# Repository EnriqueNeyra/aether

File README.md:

# Aether

### Aether is a comprehensive air quality monitor by [**Syntropy Labs**](https://syntropylabs.io/products/aether-air-quality-monitor) built around an ESP32-C3, a Sensirion SEN66 sensor, and a 3.7" e-paper display. It measures **CO2, Temperature, Humidity, PM1.0, PM2.5, PM4.0, PM10, VOC index, and NOx index**, and exposes those readings on-device, on the local network, and through Home Assistant.

## Repo Guide

| Path                      | Contents                                                                   |
| ------------------------- | -------------------------------------------------------------------------- |
| `firmware/`               | ESPHome configuration, custom components, web UI sources, and display code |
| `hardware/pcb/`           | KiCad PCB project                                                          |
| `hardware/manufacturing/` | PCB manufacturing outputs, BOM, and centroid files                         |
| `hardware/datasheets/`    | Reference datasheets used during hardware design                           |
| `enclosure/`              | SolidWorks enclosure and assembly files                                    |
| `manifests/`                  | Firmware manifests for OTA and WebUSB                      |
| `www/`                        | The combined WebUSB flasher and Quick Start Guide site     |

## Contents

- [Features](#features)
- [Hardware](#hardware)
- [Assembly](#assembly)
- [Firmware Setup](#firmware-setup)
  - [Flashing firmware onto a device](#flashing-firmware-onto-a-device)
  - [Firmware development](#firmware-development)
- [Using Aether](#using-aether)
  - [Normal operation](#normal-operation)
  - [Wi-Fi setup and behavior](#wi-fi-setup-and-behavior)
  - [Side button behavior](#side-button-behavior)
  - [Local web UI](#local-web-ui)
  - [Apple HomeKit](#apple-homekit)
  - [Home Assistant & ESPHome API](#home-assistant--esphome-api)
  - [Updates](#updates)
- [License](#license)

## Features

- Measures CO2, Temperature, Humidity, PM1.0, PM2.5, PM4.0, PM10, VOC index, and NOx index using the **Sensirion SEN66**
- Displays live readings on a **416x240 3.7" e-paper panel**
- Serves a **local web dashboard** from the device itself
- Pairs natively with **Apple HomeKit** — no hub, bridge, or Home Assistant required
- Supports **ESPHome / Home Assistant** integration
- Supports **USB factory flashing**, **firmware recovery**, and **OTA updates**
- Fully local, and can run **with or without Wi-Fi**

## Hardware

To build one Aether unit, the following core parts are needed:

| Part                                       | Link                                                                                                                                                                                                                                          |
| ------------------------------------------ | --------------------------------------------------------------------------------------------------------------------------------------------------------------------------------------------------------------------------------------------- |
| **Aether PCB**                             | [Syntropy Labs Store](https://syntropylabs.io/products/aether-air-quality-monitor-custom-pcb) (PCB files available in [`hardware/`](https://github.com/EnriqueNeyra/aether/tree/main/hardware/manufacturing) folder)                          |
| **3.7" e-paper display module**            | [Good Display](https://buy-lcd.com/products/37-inch-416x240-e-paper-black-and-white-spi-fast-refresh-electronic-eink-display-screen-esl-gdey037t03?VariantsId=10346) / [Elecrow](https://www.elecrow.com/3-7-inch-240-416-e-paper-display-black-white-e-ink-display-with-spi-communication.html?srsltid=AfmBOorEN78tDAbaNR6usiU2un_OspDES5jOZ0fWlxrPbxKdn6s-n3yS) |
| **Sensirion SEN66** air quality sensor     | [Sensirion](https://sensirion.com/products/catalog/SEN66) |
| **Reverse 6-pin JST-GH cable**             | [Adafruit](https://www.adafruit.com/product/5754?srsltid=AfmBOopcC6siE6KqjNqU-nj7AwIrnvlDSqnL19iwFrZ47O6lRIhqRYC8) / [AliExpress](https://www.aliexpress.us/w/wholesale-jst-gh-1.25mm-connector-6-pin-reverse.html?spm=a2g0o.detail.search.0) |
| **3D-printed enclosure parts**             | [`enclosure/`](https://github.com/EnriqueNeyra/aether/tree/main/enclosure) |
| **2x M3 x 6 mm countersunk screws + nuts** | [Screws](https://amzn.to/3SKvOgg) / [Nuts](https://amzn.to/44jUIG1) |

<sub>As an Amazon Associate I earn from qualifying purchases.</sub>

### Alternative Display Compatibility

The Aether PCB implements the standard 24-pin FPC e-paper interface. While designed for the 3.7" GDEY037T03, it is hardware-compatible with many other common e-paper panels (e.g., those using SSD1680, UC8151D, and IL0373 driver ICs). **Please note that these alternative displays have not yet been tested or confirmed to work with this device.**

If you choose to use an alternative display, you will need to:
1. **Update the firmware** to instantiate the correct `GxEPD2` display driver class.
2. **Modify the enclosure design** to physically fit the new panel dimensions.

For specific supported ICs and detailed firmware instructions, see [display-compatibility.md](display-compatibility.md).

## Assembly

High-level assembly flow:

### 1. Press-fit the SEN66 into the enclosure body.

### 2. Connect the e-paper display to the PCB with the FPC connector.

### 3. Press-fit the PCB into the enclosure body.

### 4. Connect 6-pin JST GH Cable.

### 5. Bring display over in position above the PCB.

### 6. Attach the display cover.

### 7. Secure the assembly from the bottom with the two M3 fasteners.

## Firmware Setup
_Any Aether devices purchased through [**Syntropy Labs**](https://syntropylabs.io/) are pre-flashed with device firmware and fully tested_

### Flashing firmware onto a device

#### For a new board or a device that needs recovery:

1. Connect Aether to your computer over USB.
2. Open the [Aether WebUSB flashing tool](https://aether.syntropylabs.io/) and go to **Firmware & Updates**.
3. Click **Install Aether firmware** under **Install or Update over USB**.
4. Keep the page open until flashing is complete.
5. Let the device boot.

#### For a device that is already set up and just needs newer firmware:

- **Over Wi-Fi (recommended):** open the device's [local web UI](#local-web-ui), go to **Firmware & updates**, and click **Update**. Home Assistant offers the same update.
- **Over USB:** follow the steps above. When the connected device is already running Aether firmware, the flasher offers an **update** that keeps your Wi-Fi and settings instead of erasing the device.

_Note: The flashing page in `www/` is built around **ESP Web Tools / Web Serial** and requires desktop **Chrome or Edge**._

### Firmware development

If you are working on the ESPHome firmware, use the **latest ESPHome release**. Releases are built with it, and CI checks every PR against it. The default PlatformIO toolchain needs Python 3.12–3.14:

```sh
pip install --upgrade esphome
git clone https://github.com/EnriqueNeyra/aether.git
cd aether/firmware
```

```sh
esphome config aether.yaml
esphome compile aether.yaml
esphome run aether.yaml
```

Release firmware can't be flashed over Wi-Fi. To iterate over Wi-Fi, flash `aether-dev.yaml` over USB once, then use `esphome run aether-dev.yaml --device <device-ip>`.

To try ESPHome's native ESP-IDF toolchain (the default once `toolchain: platformio` is removed in ESPHome 2027.2.0), pass `-s toolchain esp-idf`, e.g. `esphome -s toolchain esp-idf compile aether.yaml`.

## Using Aether

### Normal operation

Once powered, Aether reads the SEN66 and refreshes both the on-device display and the local web dashboard. Temperature can be shown in either **Fahrenheit** or **Celsius**.

### Wi-Fi setup and behavior

On boot, Aether will expose a temporary setup access point so you can connect it to Wi-Fi through the captive portal flow. The network will appear as **aether-XXXXXX**. 

- If you want **local web UI access**, **network-based ota updates**, or **Home Assistant integration**, connect the device to Wi-Fi during setup.
- If you do **not** configure Wi-Fi, the device will still work as a standalone monitor **fully offline**.

Once connected to the access point, you will automatically be redirected to the captive portal. Select your network and enter the password to connect. Once connected to Wi-Fi, the device also hosts its [local web UI](#local-web-ui) at **aether-XXXXXX.local** or the **device's local IP**.

### Side button behavior

The side / boot button supports multiple actions:

- **Short press (tap, under 1 second):** cycles normal dashboard → info screen → HomeKit setup screen → normal dashboard
- **Long press (hold ~3 seconds) from the normal screen:** enters factory reset confirmation
- **Long press (hold ~3 seconds) again on the reset screen:** confirms the factory reset flow
- **Long press (hold ~3 seconds) on the info screen while Wi-Fi is not connected:** reboots the device, which brings the setup access point back after offline mode

Long presses on the info and HomeKit screens never start a factory reset.

### Local web UI

When Aether is on your network, it serves a local browser-based dashboard directly from the device. That UI includes:

- A live environment view for sensor readings
- Temperature unit switching
- Firmware version and update status
- A way to trigger firmware updates from the device UI

### Apple HomeKit

Aether pairs directly with the Home app over Wi-Fi, with no bridge, hub or Home Assistant needed. Home Assistant keeps working alongside it.

To pair, connect Aether to the same Wi-Fi network as your iPhone, iPad or Mac, press the side button twice to show the **HomeKit Setup** screen, then in the Home app tap **+** → **Add Accessory** and scan the QR code. Each Aether has its own setup code, shown only on that screen.

Aether appears as a bridge with four accessories: Temperature, Humidity, CO2 (with an alert above 1000 ppm), and Air Quality (PM2.5, PM10, VOC and NOx, plus an overall rating from the worst of PM2.5, VOC and CO2). They also work in Home widgets, Siri and automations.

- **PM1.0 and PM4.0** aren't exposed, because HomeKit has no characteristic for them.
- **VOC and NOx** are Sensirion's unitless 1–500 indexes, but the Home app labels them in µg/m³.
- HomeKit firmware has no **Bluetooth Wi-Fi setup**, since both don't fit in flash. Use the setup network or USB instead.

### Home Assistant & ESPHome API

Because Aether runs ESPHome, it features a native API over Wi-Fi. This allows for:

- **Automatic Home Assistant Integration:** Aether will automatically appear in Home Assistant integrations dashboard once connected to your network. It exposes all 9 sensor metrics (CO2, temperature, humidity, PM1.0, PM2.5, PM4.0, PM10, VOC index, and NOx index).

<p align="center">
  
</p>

- **Custom Integrations:** You can integrate Aether into your own software or scripts using its local HTTP API. Exposed endpoints include:
  - `GET /api/state` - Returns a JSON object with all current sensor metrics and device status.
  - `POST /api/temp_unit?unit=C|F` - Changes the preferred temperature unit.
  - `POST /api/check_update` - Asks the device to re-check for a firmware update now.
  - `POST /api/perform_update` - Triggers the device to immediately begin downloading and installing the latest firmware update over HTTPS (if one is available).

### Updates

Aether supports more than one update path:

- **Local USB flashing** through the [WebUSB flashing tool](https://aether.syntropylabs.io/) (source located in `www/`)
- **In-device update flow** through the local web UI
- **Home Assistant** when the device is online

Use the USB flashing page for first-time setup and recovery. Use the local web UI for routine updates on devices that are already deployed.

## License

Aether is licensed per directory:

- **Firmware** (`firmware/`): [GNU General Public License v3](firmware/LICENSE). The firmware is built on GPLv3 code (ESPHome's C++ runtime and the GxEPD2 display driver), so it and the firmware binaries built from it are distributed under GPLv3.
- **Everything else** (hardware, PCB and manufacturing files, enclosure, website, and documentation): [Creative Commons Attribution-NonCommercial-ShareAlike 4.0 International License](http://creativecommons.org/licenses/by-nc-sa/4.0/). See [LICENSE](LICENSE).

Third-party components keep their own licenses, including the fonts in `firmware/components/aether_epaper/fonts/` and the libraries the firmware is built with.

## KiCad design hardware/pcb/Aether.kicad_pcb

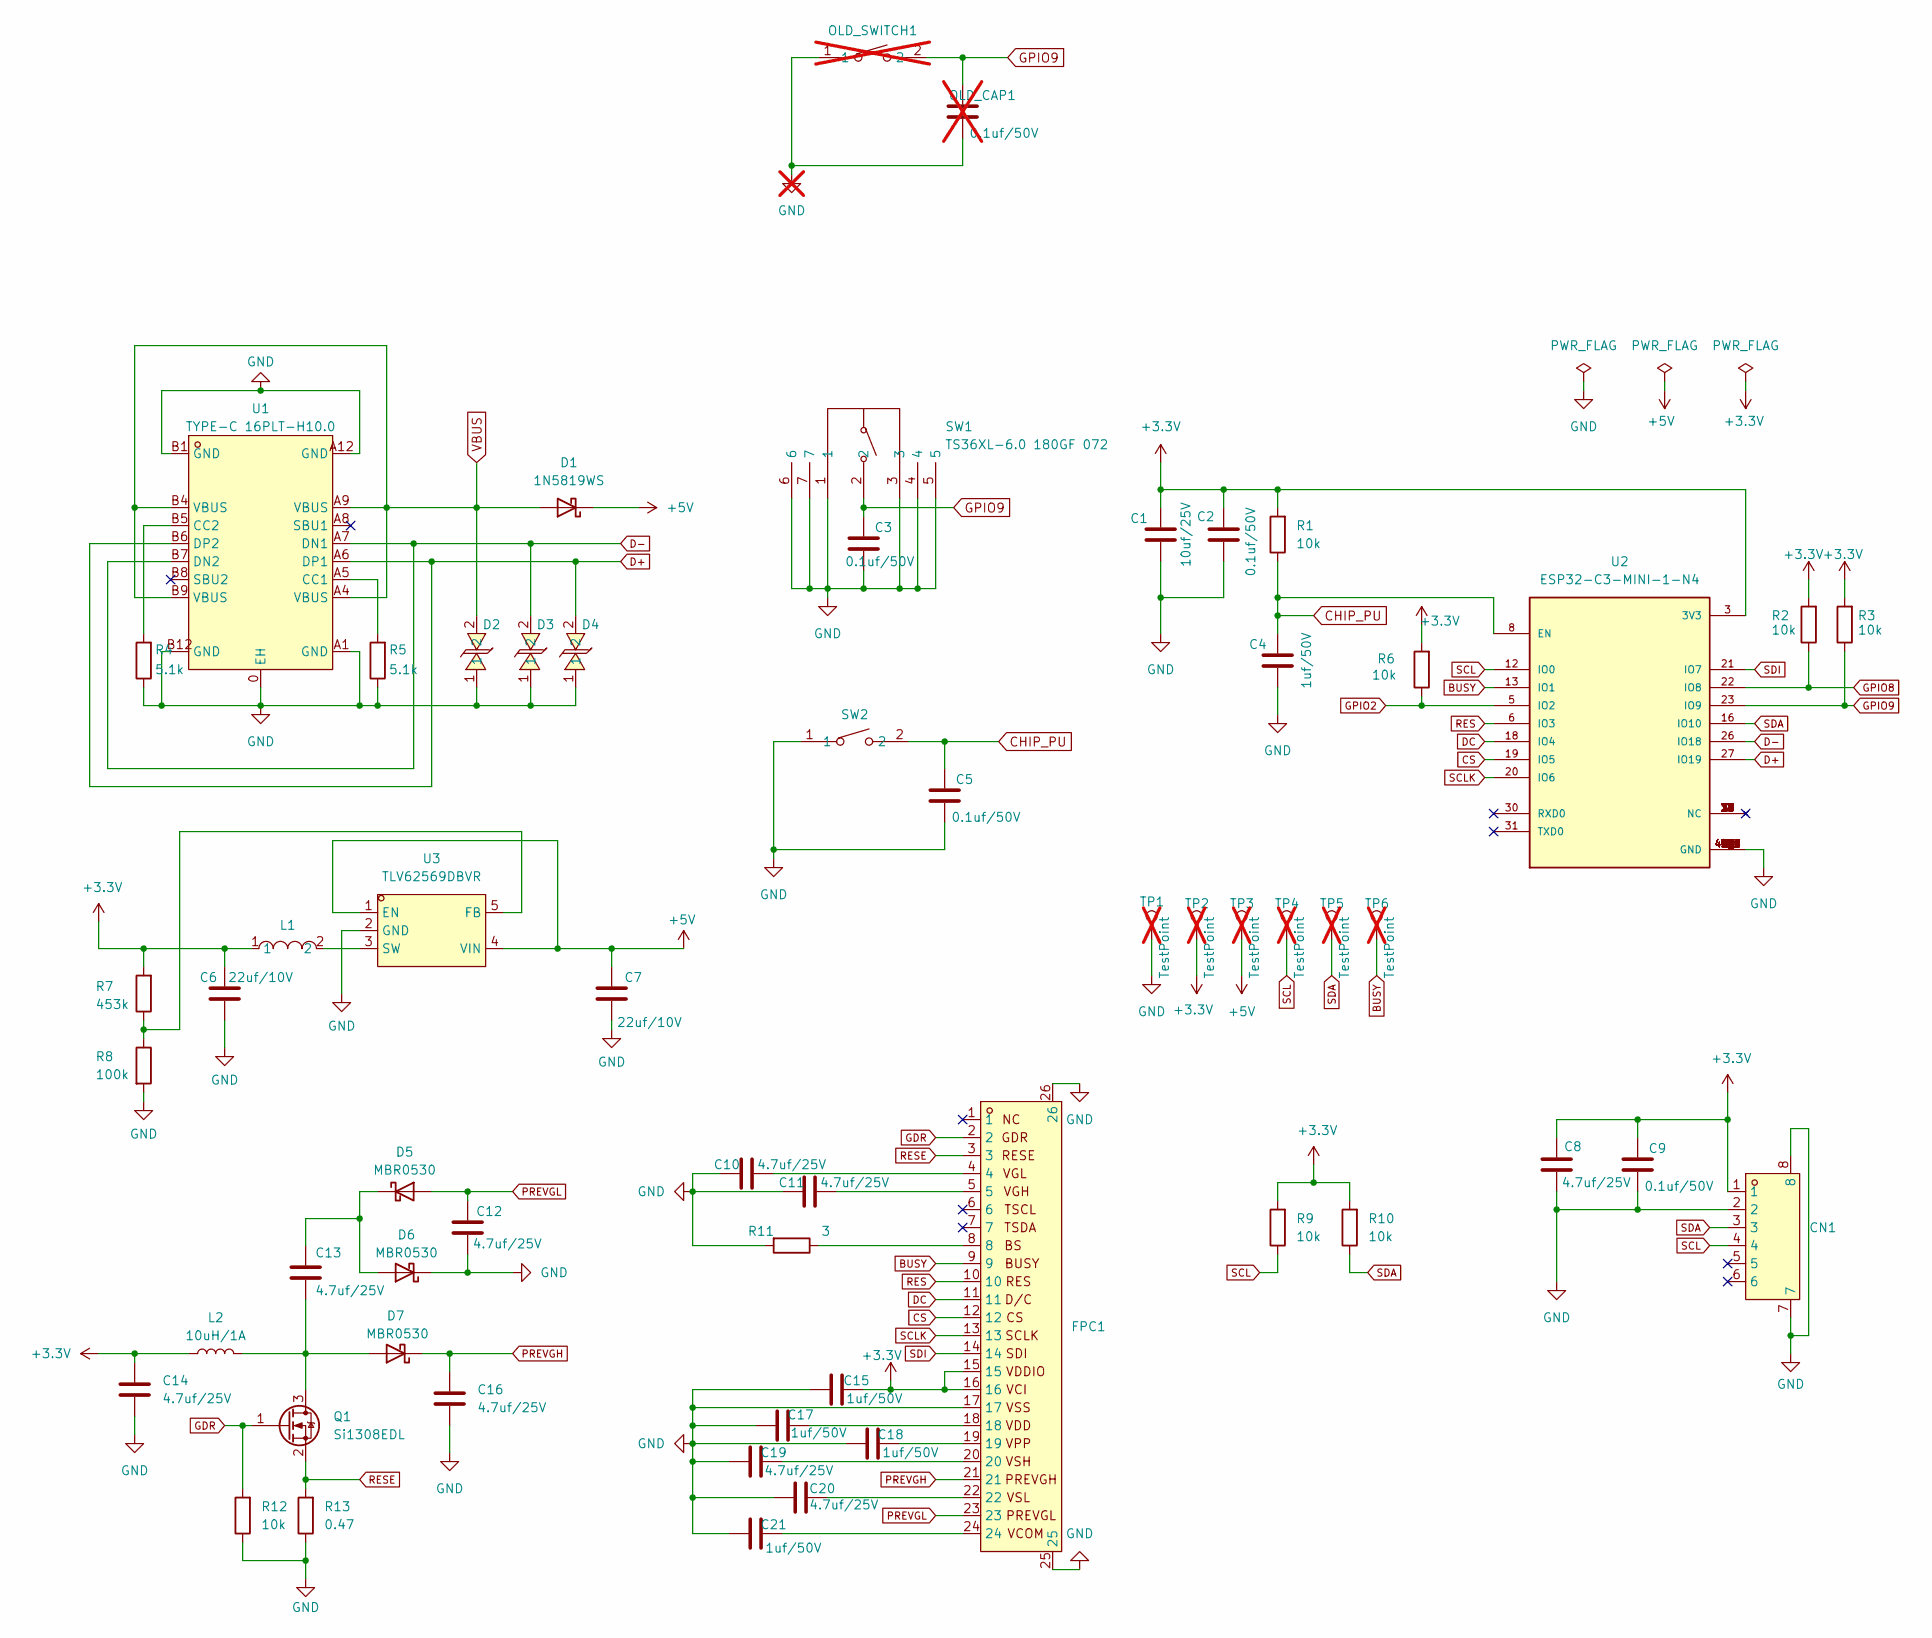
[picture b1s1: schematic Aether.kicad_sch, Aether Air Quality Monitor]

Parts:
C1: 10uf/25V; C_0603_1608Metric
C2, C3, C5, C9: 0.1uf/50V; C_0603_1608Metric
C4, C15, C17, C18, C21: 1uf/50V; C_0603_1608Metric
C6, C7: 22uf/10V; C_0603_1608Metric
C8, C10, C11, C12, C13, C14, C16, C19, C20: 4.7uf/25V; C_0603_1608Metric
CN1: SH-GH1.25-6PWB; SW-SMD_SH-GH1.25-6PWB; LCSC Part C42372473
D1: 1N5819WS; D_SOD-323
D2, D3, D4: LESD5D5.0CT1G_C5274290; SOD-523_L1.2-W0.8-LS1.6-BI; LCSC Part C5274290
D5, D6, D7: MBR0530; D_SOD-123
FPC1: FPC-05FB-24PH20; FPC-SMD_24P-P0.50_FPC-05FB-24PH20; LCSC Part C2856831
L1: NR3015S2R2MT; IND-SMD_L3.0-W3.0_NR3010; LCSC Part C42370319
L2: 10uH/1A; L_1210_3225Metric
OLD_CAP1: 0.1uf/50V; C_0603_1608Metric; not fitted
OLD_SWITCH1: TS-1088-AR02016; SW-SMD_L3.9-W3.0-P4.45; LCSC Part C720477; not fitted
Q1: Si1308EDL; SOT-323_SC-70
R1, R2, R3, R6, R9, R10, R12: 10k; R_0402_1005Metric
R4, R5: 5.1k; R_0402_1005Metric
R7: 453k; R_0603_1608Metric
R8: 100k; R_0603_1608Metric
R11: 3; R_0402_1005Metric
R13: 0.47; R_0402_1005Metric
SW1: TS36XL-6.0 180GF 072; SW-TH_SHOU-HAN_TS36XL-6.0; LCSC Part C2859427
SW2: TS-1088-AR02016; SW-SMD_L3.9-W3.0-P4.45; LCSC Part C720477
TP1, TP2, TP3, TP4, TP5, TP6: TestPoint; TestPoint_Pad_D1.5mm; not fitted
U1: TYPE-C 16PLT-H10.0; TYPE-C-SMD_USB4120-03-C; LCSC Part C3151749
U2: ESP32-C3-MINI-1-N4; XCVR_ESP32-C3-MINI-1-N4; PARTREV v1.0
U3: TLV62569DBVR; SOT-23-5_L3.0-W1.7-P0.95-LS2.8-BR; LCSC Part C141836

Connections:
+3.3V: C1.2, C2.1, C6.2, C8.2, C9.1, C14.1, C15.2, CN1.1, FPC1.15, FPC1.16, L1.1, L2.1, R1.2, R2.2, R3.2, R6.2, R7.2, R9.2, R10.2, TP2.1, U2.3 (3V3)
+5V: C7.1, D1.1 (K), TP3.1, U3.1 (EN), U3.4 (VIN)
BUSY: FPC1.9, TP6.1, U2.13 (IO1)
CHIP_PU: C4.2, C5.1, R1.1, SW2.2, U2.8 (EN)
CS: FPC1.12, U2.19 (IO5)
D+: D4.2, U1.A6 (DP1), U1.B6 (DP2), U2.27 (IO19)
D-: D3.2, U1.A7 (DN1), U1.B7 (DN2), U2.26 (IO18)
DC: FPC1.11, U2.18 (IO4)
GDR: FPC1.2, Q1.1 (G), R12.2
GND: C1.1, C2.2, C3.2, C4.1, C5.2, C6.1, C7.2, C8.1, C9.2, C10.1, C11.1, C12.2, C14.2, C15.1, C16.2, C17.2, C18.2, C19.1, C20.1, C21.1, CN1.2, CN1.7, CN1.8, D2.1, D3.1, D4.1, D6.1 (K), FPC1.17, FPC1.25, FPC1.26, OLD_CAP1.2, OLD_SWITCH1.1, R4.1, R5.1, R8.2, R11.2, R12.1, R13.1, SW1.1, SW1.3, SW1.4, SW1.5, SW1.6, SW1.7, SW2.1, TP1.1, U1.0 (EH), U1.A1 (GND), U1.A12 (GND), U1.B1 (GND), U1.B12 (GND), U2.1 (GND), U2.2 (GND), U2.11 (GND), U2.14 (GND), U2.36 (GND), U2.37 (GND), U2.38 (GND), U2.39 (GND), U2.40 (GND), U2.41 (GND), U2.42 (GND), U2.43 (GND), U2.44 (GND), U2.45 (GND), U2.46 (GND), U2.47 (GND), U2.48 (GND), U2.49_1 (GND), U2.49_2 (GND), U2.49_3 (GND), U2.49_4 (GND), U2.49_5 (GND), U2.49_6 (GND), U2.49_7 (GND), U2.49_8 (GND), U2.49_9 (GND), U2.50 (GND), U2.51 (GND), U2.52 (GND), U2.53 (GND), U3.2 (GND)
GPIO2: R6.1, U2.5 (IO2)
GPIO8: R2.1, U2.22 (IO8)
GPIO9: C3.1, OLD_CAP1.1, OLD_SWITCH1.2, R3.1, SW1.2, U2.23 (IO9)
unnamed: C10.2, FPC1.4
unnamed: C11.2, FPC1.5
unnamed: C17.1, FPC1.18
unnamed: C18.1, FPC1.19
unnamed: C19.2, FPC1.20
unnamed: C20.2, FPC1.22
unnamed: C21.2, FPC1.24
unnamed: C13.1, D5.1 (K), D6.2 (A)
unnamed: C13.2, D7.2 (A), L2.2, Q1.3 (D)
unnamed: FPC1.8, R11.1
unnamed: R5.2, U1.A5 (CC1)
unnamed: R4.2, U1.B5 (CC2)
unnamed: R7.1, R8.1, U3.5 (FB)
unnamed: L1.2, U3.3 (SW)
PREVGH: C16.1, D7.1 (K), FPC1.21
PREVGL: C12.1, D5.2 (A), FPC1.23
RES: FPC1.10, U2.6 (IO3)
RESE: FPC1.3, Q1.2 (S), R13.2
SCL: CN1.4, R9.1, TP4.1, U2.12 (IO0)
SCLK: FPC1.13, U2.20 (IO6)
SDA: CN1.3, R10.1, TP5.1, U2.16 (IO10)
SDI: FPC1.14, U2.21 (IO7)
VBUS: D1.2 (A), D2.2, U1.A4 (VBUS), U1.A9 (VBUS), U1.B4 (VBUS), U1.B9 (VBUS)

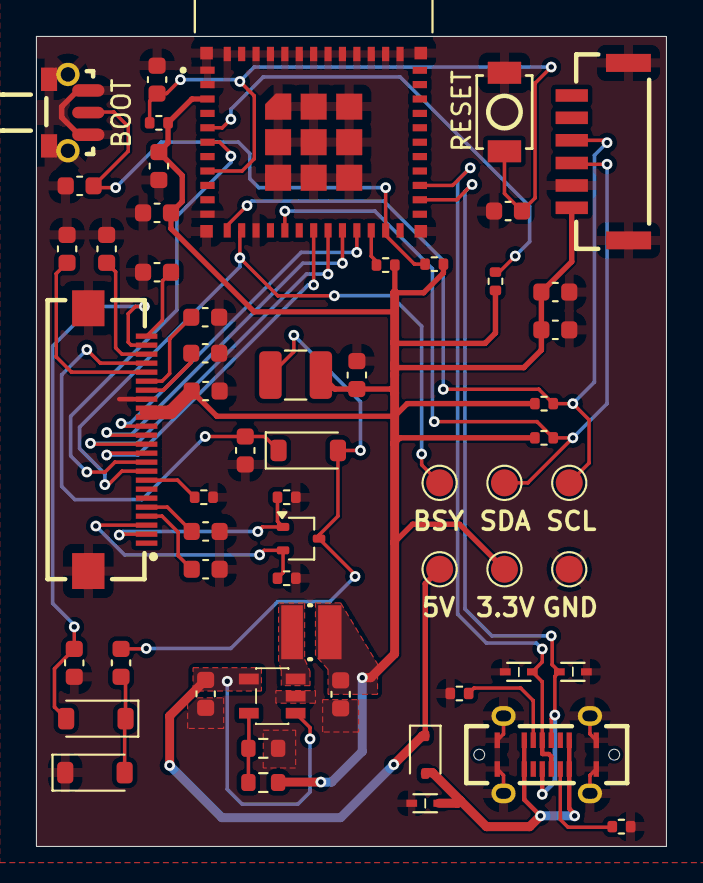
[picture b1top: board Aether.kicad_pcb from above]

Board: 2 copper layers, 35.0 x 45.0 mm, 57 parts (0 on the bottom side), 36 nets.

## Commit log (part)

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2026-03-14 Populate all inital firmware files
2026-03-14 add gitignore for esphome
2026-03-18 Improvements to epaper rendering to support unit symbols, adding agents.md
2026-04-19 - Overhaul display, web UI, and device config - Rewrote e-paper rendering with proper layout system, boot animation, info screen with QR codes, and factory reset flow - Split web UI out of inline C++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
2026-04-19 Populate all current KiCAD and Solidworks files
2026-04-19 epaper display refactoring
2026-04-19 update manifest url
2026-04-19 manifest update and yaml fix
2026-04-19 manifest update
2026-04-20 increment version
2026-04-20 update yaml firmware version
2026-05-06 Create CNAME
2026-05-06 minor firmware updates, added firmware flashing tool, modify manifest files for OTA and factory flashing
2026-05-07 Update agents.md, add github action for pages
2026-05-07 Add release workflow, remove temp solidworks files,
2026-05-07 Release v1.0.3 [skip release]
2026-06-16 Add initial README version, add periodic full refresh, update local web UI styling, update flasher UI for styling consistency
2026-06-16 Release v1.0.4 [skip release]
2026-06-16 Update readme [skip release]
2026-06-16 Update README.md [skip release]
2026-06-20 Update fonts, readme update
2026-06-20 Release v1.0.5 [skip release]
2026-06-20 update local web ui and captive portal handling
2026-06-20 Release v1.0.6 [skip release]
2026-06-20 improve pages deplyment and update flow
2026-06-20 Release v1.0.7 [skip release]
2026-06-20 Improve local web UI, fix redundant pages release in workflow
2026-06-20 Release v1.0.8 [skip release]
2026-06-20 Consolidate web assets, add info about display compatabilty, pipeline and manifest updates
2026-06-20 readme edit
2026-06-20 display compatability edit
2026-06-20 Release v1.0.9 [skip release]
2026-06-20 update pages workflow
2026-06-20 Release v1.0.10 [skip release]
2026-06-21 Update aether web page instructions
2026-06-21 Release v1.0.11 [skip release]
2026-06-22 update web assets [skip release]
2026-06-22 update cad files
2026-06-22 Release v1.0.12 [skip release]

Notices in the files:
README.md:
License: CC BY-NC-SA 4.0
